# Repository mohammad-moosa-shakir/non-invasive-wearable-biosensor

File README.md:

# non-invasive-wearable-biosensor
The KiCAD files for a hypothetical Non-Invasive Wearable Biosensor for Mice.

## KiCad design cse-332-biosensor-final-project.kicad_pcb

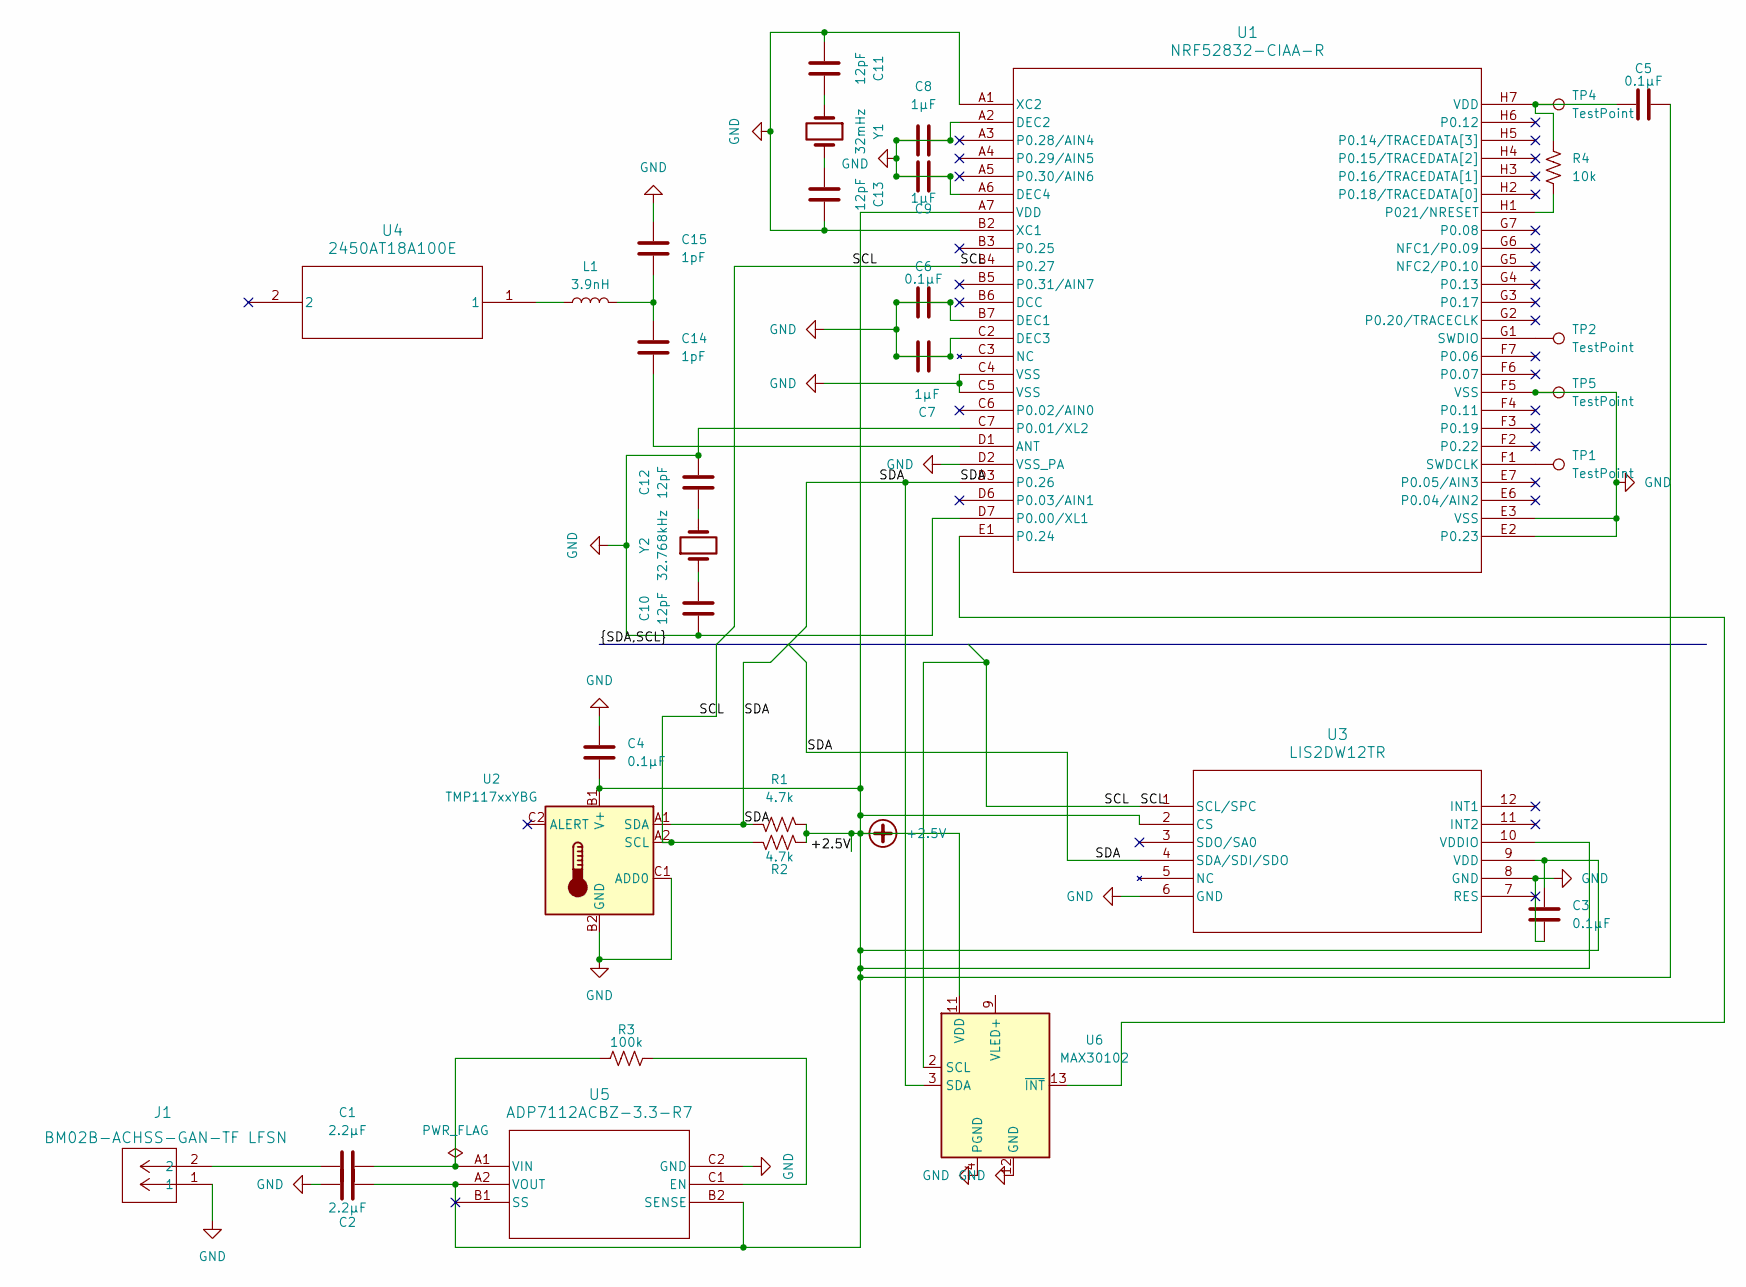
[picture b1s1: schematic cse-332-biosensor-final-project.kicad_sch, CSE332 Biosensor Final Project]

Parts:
C1, C2: 2.2µF; C_0201_0603Metric
C3, C4, C5, C6: 0.1µF; C_0201_0603Metric
C7, C8, C9: 1µF; C_0201_0603Metric
C10, C11, C12, C13: 12pF; C_0201_0603Metric
C14, C15: 1pF; C_0201_0603Metric
J1: BM02B-ACHSS-GAN-TF LFSN; CONN_BM02B-ACHSS-GAN-TF_JST
L1: 3.9nH; L_0201_0603Metric
R1, R2: 4.7k; R_0201_0603Metric
R3: 100k; R_0201_0603Metric
R4: 10k; R_0201_0603Metric
TP1, TP2, TP4, TP5: TestPoint; TestPoint_Pad_D1.0mm
U1: NRF52832-CIAA-R; WLCSP50_2P956X3P226_NOR
U2: TMP117xxYBG; Texas_DSBGA-6_0.95x1.488mm_Layout2x3_P0.4mm
U3: LIS2DW12TR; LGA-12_2X2X0P7_STM
U4: 2450AT18A100E; 2450AT18A100E_JOT
U5: ADP7112ACBZ-3.3-R7; CB-6-15_ADI
U6: MAX30102; Maxim_OLGA-14_3.3x5.6mm_P0.8mm
Y1: 32mHz; Crystal_SMD_1210-4Pin_1.2x1.0mm
Y2: 32.768kHz; Crystal_SMD_3215-2Pin_3.2x1.5mm

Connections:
+2.5V: C2.1, C3.2, C4.1, C5.1, R1.2, R2.2, U1.A7 (VDD), U2.B1 (V+), U3.2 (CS), U3.9 (VDD), U3.10 (VDDIO), U5.A2 (VOUT), U5.B2 (SENSE), U6.11 (VDD)
/SCL: R2.1, U1.B4 (P0.27), U2.A2 (SCL), U3.1 (SCL/SPC), U6.2 (SCL)
/SDA: R1.1, U1.D3 (P0.26), U2.A1 (SDA), U3.4 (SDA/SDI/SDO), U6.3 (SDA)
GND: C2.2, C3.1, C4.2, C6.1, C6.2, C7.1, C7.2, C8.1, C8.2, C9.1, C9.2, C10.2, C11.2, C12.1, C13.2, C15.1, J1.1, TP5.1, U1.A1 (XC2), U1.A2 (DEC2), U1.A6 (DEC4), U1.B2 (XC1), U1.B7 (DEC1), U1.C2 (DEC3), U1.C4 (VSS), U1.C5 (VSS), U1.C7 (P0.01/XL2), U1.D2 (VSS_PA), U1.D7 (P0.00/XL1), U1.E2 (P0.23), U1.E3 (VSS), U1.F5 (VSS), U2.B2 (GND), U2.C1 (ADD0), U3.6 (GND), U3.8 (GND), U5.C2 (GND), U6.4 (PGND), U6.12 (GND)
unnamed: C1.2, J1.2
unnamed: C5.2, R4.1, TP4.1, U1.H7 (VDD)
unnamed: C10.1, Y2.1
unnamed: C11.1, Y1.1
unnamed: C12.2, Y2.2
unnamed: C13.1, Y1.2
unnamed: C14.1, C15.2, L1.2
unnamed: L1.1, U4.1
unnamed: C14.2, U1.D1 (ANT)
unnamed: U1.E1 (P0.24), U6.13 (~INT)
unnamed: R4.2, U1.H1 (P021/NRESET)
unnamed: TP1.1, U1.F1 (SWDCLK)
unnamed: TP2.1, U1.G1 (SWDIO)
unnamed: R3.2, U5.C1 (EN)
unnamed: C1.1, R3.1, U5.A1 (VIN)
unnamed: U6.9 (VLED+), U6.10 (VLED+)

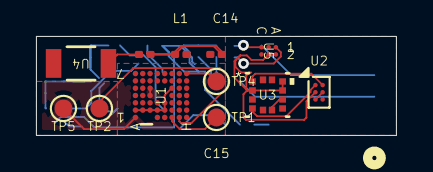
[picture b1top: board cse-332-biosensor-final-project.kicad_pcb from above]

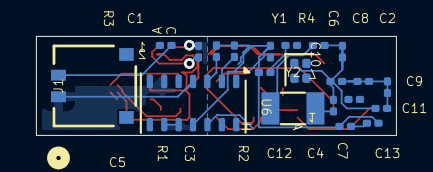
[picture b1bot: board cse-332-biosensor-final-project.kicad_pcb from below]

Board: 2 copper layers, 20.0 x 5.5 mm, 33 parts (21 on the bottom side), 20 nets.

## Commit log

2026-04-10 Added KiCad Files Via Upload
